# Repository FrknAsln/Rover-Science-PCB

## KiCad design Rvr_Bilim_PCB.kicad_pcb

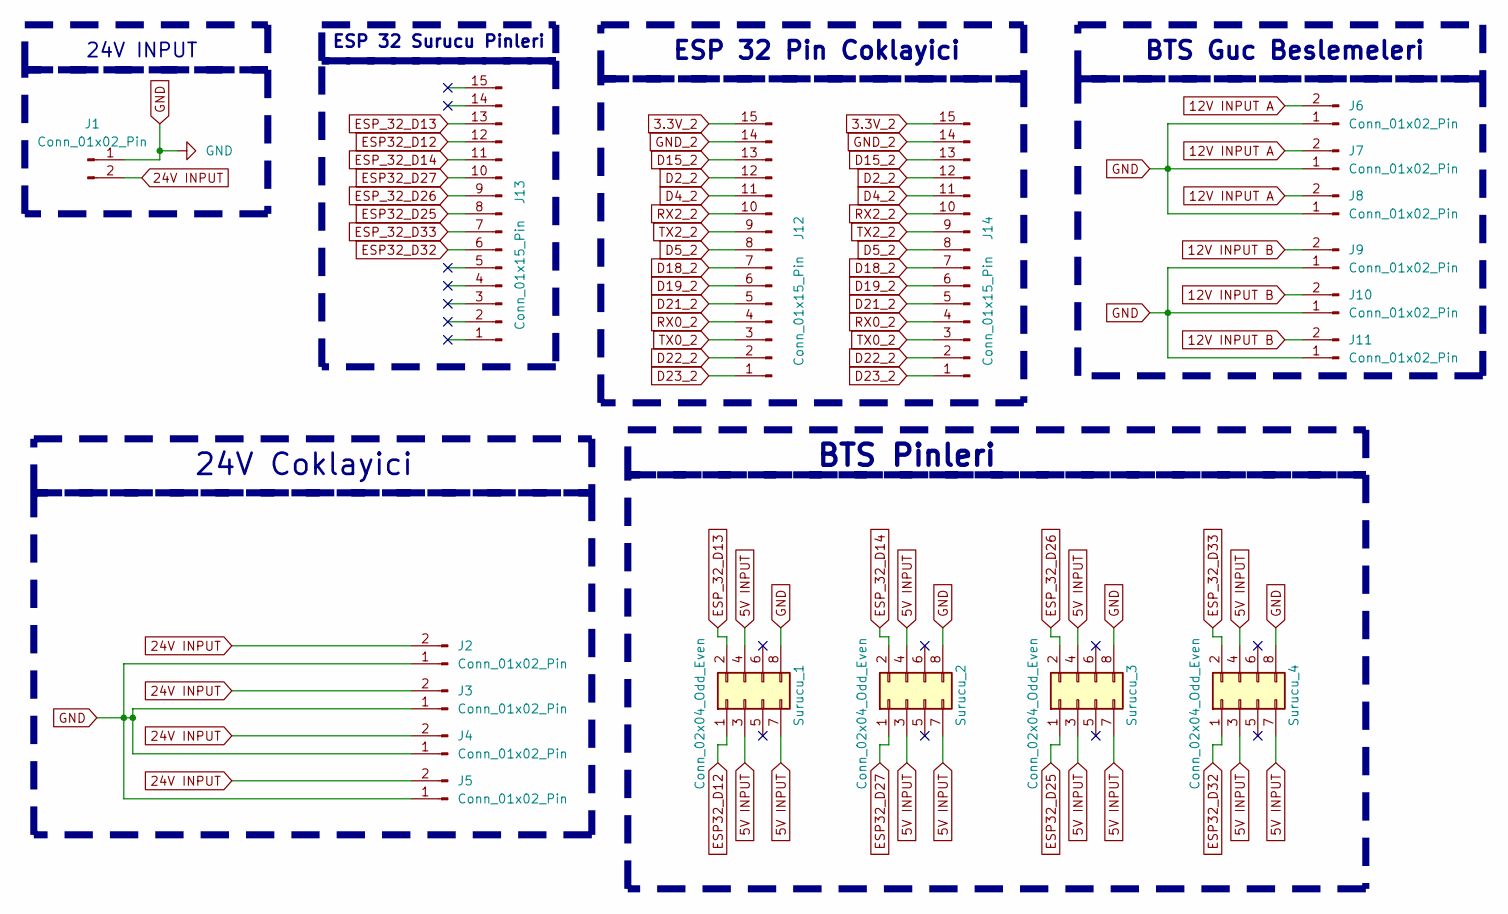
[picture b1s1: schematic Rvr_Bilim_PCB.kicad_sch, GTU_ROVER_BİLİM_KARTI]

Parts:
J1: Conn_01x02_Pin; XT90PBF
J2, J3, J4, J5, J6, J7, J8, J9, J10, J11: Conn_01x02_Pin; AMASS_XT30UPB-F_1x02_P5.0mm_Vertical
J12, J13, J14: Conn_01x15_Pin; PinSocket_1x15_P2.54mm_Vertical
Surucu_1, Surucu_2, Surucu_3, Surucu_4: Conn_02x04_Odd_Even; PinSocket_2x04_P2.54mm_Vertical

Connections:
3.3V_2: J12.15, J14.15
5V INPUT: Surucu_1.3, Surucu_1.4, Surucu_1.7, Surucu_2.3, Surucu_2.4, Surucu_2.7, Surucu_3.3, Surucu_3.4, Surucu_3.7, Surucu_4.3, Surucu_4.4, Surucu_4.7
12V INPUT A: J6.2, J7.2, J8.2
12V INPUT B: J9.2, J10.2, J11.2
24V INPUT: J1.2, J2.2, J3.2, J4.2, J5.2
D2_2: J12.12, J14.12
D4_2: J12.11, J14.11
D5_2: J12.8, J14.8
D15_2: J12.13, J14.13
D18_2: J12.7, J14.7
D19_2: J12.6, J14.6
D21_2: J12.5, J14.5
D22_2: J12.2, J14.2
D23_2: J12.1, J14.1
ESP32_D12: J13.12, Surucu_1.1
ESP32_D25: J13.8, Surucu_3.1
ESP32_D27: J13.10, Surucu_2.1
ESP32_D32: J13.6, Surucu_4.1
ESP_32_D13: J13.13, Surucu_1.2
ESP_32_D14: J13.11, Surucu_2.2
ESP_32_D26: J13.9, Surucu_3.2
ESP_32_D33: J13.7, Surucu_4.2
GND: J1.1, J2.1, J3.1, J4.1, J5.1, J6.1, J7.1, J8.1, J9.1, J10.1, J11.1, Surucu_1.8, Surucu_2.8, Surucu_3.8, Surucu_4.8
GND_2: J12.14, J14.14
RX0_2: J12.4, J14.4
RX2_2: J12.10, J14.10
TX0_2: J12.3, J14.3
TX2_2: J12.9, J14.9

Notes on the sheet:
24V Coklayici
24V INPUT
BTS Guc Beslemeleri
ESP 32 Pin Coklayici
BTS Pinleri
ESP 32 Surucu Pinleri

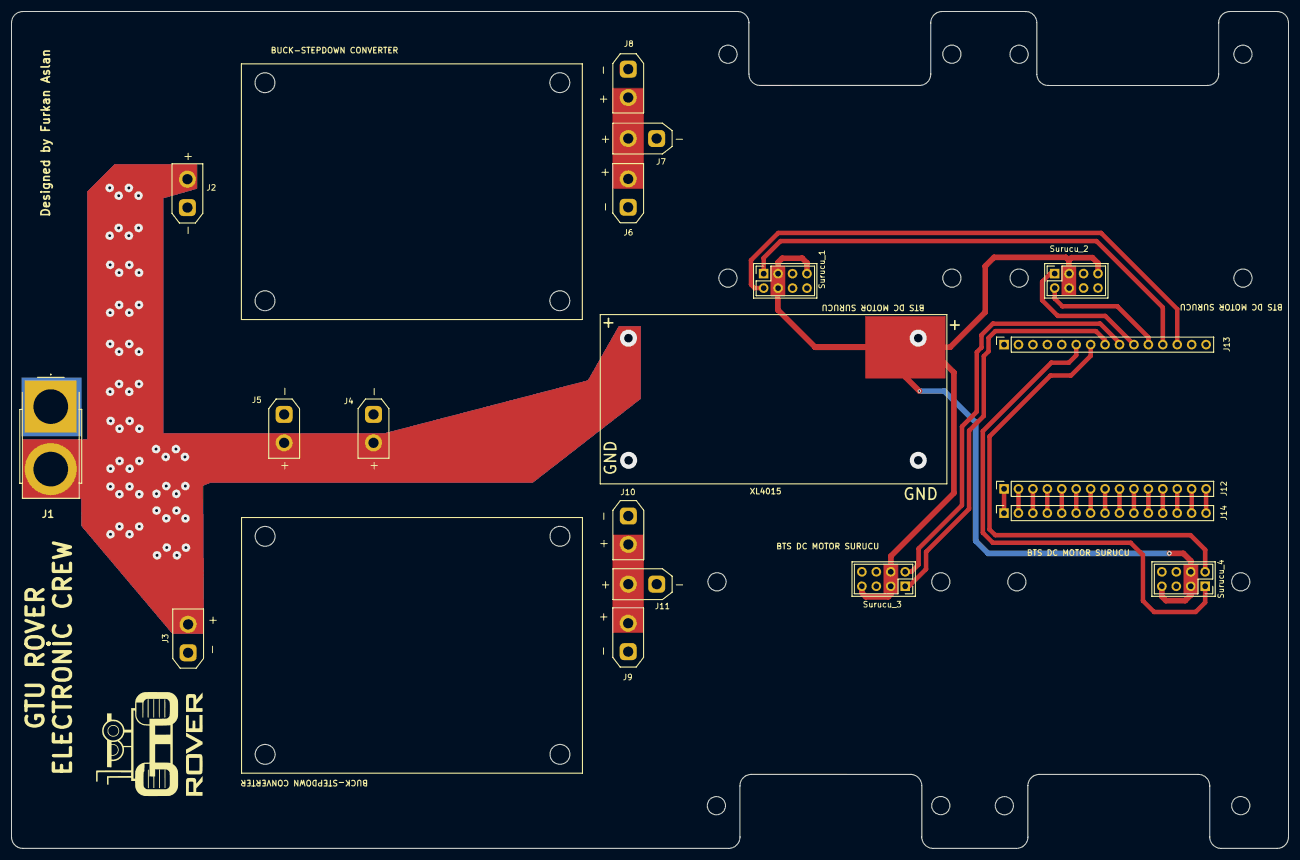
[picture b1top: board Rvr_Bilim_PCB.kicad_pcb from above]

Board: 2 copper layers, 224.8 x 147.3 mm, 18 parts (0 on the bottom side), 28 nets.
